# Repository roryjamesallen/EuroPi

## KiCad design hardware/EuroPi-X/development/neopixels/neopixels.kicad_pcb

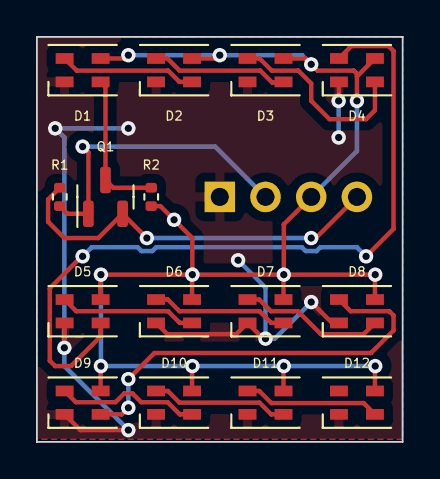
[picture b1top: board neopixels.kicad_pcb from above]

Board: 2 copper layers, 20.3 x 22.5 mm, 16 parts (1 on the bottom side), 16 nets.

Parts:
D1, D2, D3, D4, D5, D6, D7, D8, D9, D10, D11, D12: SK6805; LED_SK6805_PLCC4_2.4x2.7mm_P1.3mm
J1: Conn_01x04_Pin; PinHeader_1x04_P2.54mm_Vertical
Q1: BSS138; SOT-23
R1, R2: 10K; R_0402_1005Metric

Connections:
+3.3V: J1.2, Q1.1 (G), R1.1
+5V: D1.4 (VDD), D2.4 (VDD), D3.4 (VDD), D4.4 (VDD), D5.4 (VDD), D6.4 (VDD), D7.4 (VDD), D8.4 (VDD), D9.4 (VDD), D10.4 (VDD), D11.4 (VDD), D12.4 (VDD), J1.3, R2.1
/DATA_IN: J1.4, Q1.2 (S), R1.2
Earth: D1.2 (VSS), D2.2 (VSS), D3.2 (VSS), D4.2 (VSS), D5.2 (VSS), D6.2 (VSS), D7.2 (VSS), D8.2 (VSS), D9.2 (VSS), D10.2 (VSS), D11.2 (VSS), D12.2 (VSS), J1.1
unnamed: D1.3 (DIN), Q1.3 (D), R2.2
unnamed: D1.1 (DOUT), D2.3 (DIN)
unnamed: D2.1 (DOUT), D3.3 (DIN)
unnamed: D3.1 (DOUT), D4.3 (DIN)
unnamed: D4.1 (DOUT), D5.3 (DIN)
unnamed: D5.1 (DOUT), D6.3 (DIN)
unnamed: D6.1 (DOUT), D7.3 (DIN)
unnamed: D7.1 (DOUT), D8.3 (DIN)
unnamed: D8.1 (DOUT), D9.3 (DIN)
unnamed: D9.1 (DOUT), D10.3 (DIN)
unnamed: D10.1 (DOUT), D11.3 (DIN)
unnamed: D11.1 (DOUT), D12.3 (DIN)

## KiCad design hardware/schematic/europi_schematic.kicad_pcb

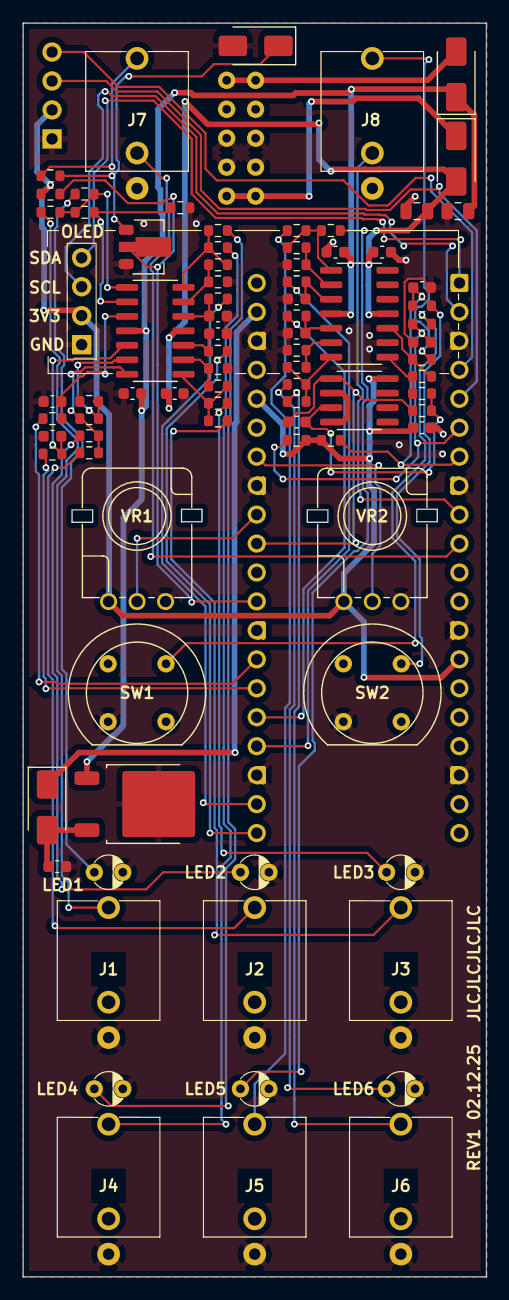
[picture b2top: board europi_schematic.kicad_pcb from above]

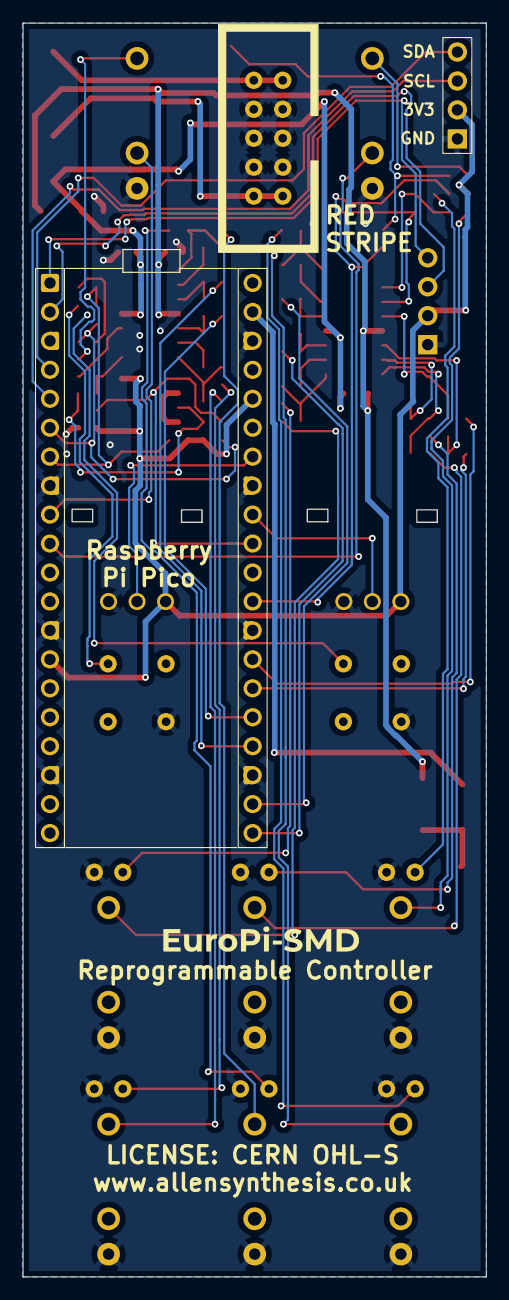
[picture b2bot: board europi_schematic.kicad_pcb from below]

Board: 2 copper layers, 40.6 x 110.0 mm, 88 parts (3 on the bottom side), 64 nets.

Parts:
C1, C2: 10uF; C_0805_2012Metric
C3: 1uF; C_0603_1608Metric
C4, C5, C6, C7, C9, C10, C11, C12, C13, C14, C16, C17, C18: 100nF; C_0603_1608Metric
C15: 1nF; C_0603_1608Metric
D1, D2, D3, D5: D; D_SMA
J1: Conn_02x05_Odd_Even; power-header-10-pin-unlabelled
J2, J11: Conn_01x04_Pin; PinHeader_1x04_P2.54mm_Vertical
J3: Output 1 Jack; jack-thonkiconn-mono
J4: Output 4 Jack; jack-thonkiconn-mono
J5: Analogue Input Jack; jack-thonkiconn-mono
J6: Output 2 Jack; jack-thonkiconn-mono
J7: Output 5 Jack; jack-thonkiconn-mono
J8: Digital Input Jack; jack-thonkiconn-mono
J9: Output 3 Jack; jack-thonkiconn-mono
J10: Output 6 Jack; jack-thonkiconn-mono
LED1, LED2, LED3, LED4, LED5, LED6: LED; led-3mm
Q1: 2N2222; SOT-89-3
R1, R2, R3, R4, R13, R14, R16, R17, R26, R27, R29, R30, R38, R39: 1K; R_0603_1608Metric
R5, R6, R40: 10K; R_0603_1608Metric
R7, R8, R15, R19, R20, R31, R32, R35: 100K; R_0603_1608Metric
R9, R10, R21, R22, R33, R34: 220K; R_0603_1608Metric
R11, R12, R24, R25, R36, R37: 4K7; R_0603_1608Metric
R18, R23, R28: 22K; R_0603_1608Metric
SW1, SW2: SW_Push; switch-momentary-c&k
U2: PICO_RP2040; raspberry-pi-pico
U3, U4: TL074; SOIC-14_3.9x8.7mm_P1.27mm
U5: MCP6002-xSN; SOIC-8_3.9x4.9mm_P1.27mm
U6: L7805; TO-252-2
VR1: KNOB 1; potentiometer-9mm
VR2: KNOB 2; potentiometer-9mm

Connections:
+3.3V: C18.1, J2.2, J11.2, R5.2, R6.2, R40.1, U2.14 (GP10), U2.36 (3V3), U5.8 (V+), VR1.1, VR2.1
+5V: C3.1, D2.2 (A), U6.3 (OUT)
+12V: C1.1, C4.1, C6.1, D5.1 (K), U3.4 (V+), U4.4 (V+), U6.1 (IN)
-12V: C2.2, C5.2, C7.2, D1.2 (A), U3.11 (V-), U4.11 (V-)
AIN_DETECT: J5.2 (TN), U2.9 (GP6)
ANALOGUE_IN: C15.2, R28.2, U2.31 (GP26), U5.1
BUTTON_1: C9.1, R1.1, R5.1, U2.6 (GP4)
BUTTON_2: C10.1, R2.1, R6.1, U2.7 (GP5)
DIGITAL_IN: Q1.2 (C), R40.2, U2.29 (GP22)
DIN_DETECT: J8.2 (TN), U2.10 (GP7)
GND: C1.2, C2.1, C3.2, C4.2, C5.1, C6.2, C7.1, C9.2, C10.2, C11.2, C12.2, C13.2, C14.2, C16.2, C17.2, C18.2, D3.2 (A), J1.3, J1.4, J1.5, J1.6, J1.7, J1.8, J2.1, J3.1 (E), J4.1 (E), J5.1 (E), J6.1 (E), J7.1 (E), J8.1 (E), J9.1 (E), J10.1 (E), J11.1, LED1.1 (K), LED2.1 (K), LED3.1 (K), LED4.1 (K), LED5.1 (K), LED6.1 (K), Q1.3 (E), R7.2, R8.2, R19.2, R20.2, R31.2, R32.2, SW1.1, SW2.1, U2.3 (GND), U2.8 (GND), U2.13 (GND), U2.18 (GND), U2.23 (GND), U2.28 (GND), U2.33 (GND), U2.38 (GND), U4.9 (-), U5.2 (-), U5.4 (V-), U6.2 (GND), VR1.3, VR2.3
I2C_SCL: J11.3, U2.5 (GP3)
I2C_SDA: J11.4, U2.4 (GP2)
KNOB_1: U2.32 (GP27), VR1.2
KNOB_2: U2.34 (GP28), VR2.2
unnamed: D1.1 (K), J1.1, J1.2
unnamed: D2.1 (K), U2.39 (VSYS)
unnamed: D3.1 (K), Q1.1 (B), R35.2
unnamed: D5.2 (A), J1.9, J1.10
unnamed: J3.3 (T), R13.2
unnamed: J4.3 (T), R14.2
unnamed: J5.3 (T), R15.1
unnamed: J6.3 (T), R26.2
unnamed: J7.3 (T), R27.2
unnamed: J8.3 (T), R35.1
unnamed: J9.3 (T), R38.2
unnamed: J10.3 (T), R39.2
unnamed: LED1.2 (A), R11.1
unnamed: LED2.2 (A), R12.1
unnamed: LED3.2 (A), R24.1
unnamed: LED4.2 (A), R25.1
unnamed: LED5.2 (A), R36.1
unnamed: LED6.2 (A), R37.1
unnamed: R1.2, SW1.2
unnamed: R2.2, SW2.2
unnamed: R10.1, R12.2, R14.1, U3.14
unnamed: R9.1, R11.2, R13.1, U3.1
unnamed: R18.2, R23.1, U4.8
unnamed: R21.1, R24.2, R26.1, U3.7
unnamed: R22.1, R25.2, R27.1, U4.1
unnamed: R33.1, R36.2, R38.1, U3.8
unnamed: R34.1, R37.2, R39.1, U4.7
unnamed: C11.1, R3.1, U3.3 (+)
unnamed: R7.1, R9.2, U3.2 (-)
unnamed: C13.1, R16.1, U3.5 (+)
unnamed: R19.1, R21.2, U3.6 (-)
unnamed: C16.1, R29.1, U3.10 (+)
unnamed: R31.1, R33.2, U3.9 (-)
unnamed: C12.1, R4.1, U3.12 (+)
unnamed: R8.1, R10.2, U3.13 (-)
unnamed: C14.1, R17.1, U4.3 (+)
unnamed: R20.1, R22.2, U4.2 (-)
unnamed: C17.1, R30.1, U4.5 (+)
unnamed: R32.1, R34.2, U4.6 (-)
unnamed: R15.2, R18.1, U4.10 (+)
unnamed: C15.1, R23.2, R28.1, U5.3 (+)
OLED_SCL: J2.3, U2.2 (GP1)
OLED_SDA: J2.4, U2.1 (GP0)
OUT_1: R3.2, U2.27 (GP21)
OUT_2: R16.2, U2.26 (GP20)
OUT_3: R29.2, U2.21 (GP16)
OUT_4: R4.2, U2.22 (GP17)
OUT_5: R17.2, U2.24 (GP18)
OUT_6: R30.2, U2.25 (GP19)

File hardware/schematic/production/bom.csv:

Designator,Footprint,Quantity,Value,LCSC Part #
"C1, C2",0805,2,10uF,
"C10, C11, C12, C13, C14, C16, C17, C18, C4, C5, C6, C7, C9",0603,13,100nF,
C15,0603,1,1nF,
C3,0603,1,1uF,
"D1, D2, D5",D_SMA,3,D,C5356810
D3,D_SMA,1,D,
J1,power-header-10-pin-unlabelled,1,Conn_02x05_Odd_Even,
J10,jack-thonkiconn-mono,1,Output 6 Jack,
"J11, J2",PinHeader_1x04_P2.54mm_Vertical,2,Conn_01x04_Pin,
J3,jack-thonkiconn-mono,1,Output 1 Jack,
J4,jack-thonkiconn-mono,1,Output 4 Jack,
J5,jack-thonkiconn-mono,1,Analogue Input Jack,
J6,jack-thonkiconn-mono,1,Output 2 Jack,
J7,jack-thonkiconn-mono,1,Output 5 Jack,
J8,jack-thonkiconn-mono,1,Digital Input Jack,
J9,jack-thonkiconn-mono,1,Output 3 Jack,
"LED1, LED2, LED3, LED4, LED5, LED6",led-3mm,6,LED,
Q1,SOT-89-3,1,2N2222,C21714170
"R1, R13, R14, R16, R17, R2, R26, R27, R29, R3, R30, R38, R39, R4",0603,14,1K,
"R10, R21, R22, R33, R34, R9",0603,6,220K,
"R11, R12, R24, R25, R36, R37",0603,6,4K7,
"R15, R19, R20, R31, R32, R35, R7, R8",0603,8,100K,
"R18, R23, R28",0603,3,22K,
"R40, R5, R6",0603,3,10K,
"SW1, SW2",switch-momentary-c&k,2,SW_Push,
U2,raspberry-pi-pico,1,PICO_RP2040,
"U3, U4",SOIC-14_3.9x8.7mm_P1.27mm,2,TL074,C6963
U5,SOIC-8_3.9x4.9mm_P1.27mm,1,MCP6002-xSN,C7377
U6,TO-252-2,1,L7805,C7394043
VR1,potentiometer-9mm,1,KNOB 1,
VR2,potentiometer-9mm,1,KNOB 2,

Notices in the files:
hardware/schematic/europi_schematic.kicad_pcb:
LICENSE: CERN OHL-S
